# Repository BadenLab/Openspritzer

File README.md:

<p align="right">
<h1 align="center">Openspritzer</h1></p>
<h3 align="center">An open hardware pressure ejection system for reliably delivering picolitre volumes.</h3>
<p align="center"><h6 align="right">by C.J. Forman, H. Tomes, B. Mbobo, R.J. Burman, M. Jacobs, T Baden &
J.V. Raimondo</h6></p>
<p align="center"><h6 align="right">adapted by M.J.Y. Zimmermann</h6></p>

</p>

<p align="justify">Designed for ease of use, robustness and low-cost, the “Openspritzer” is an open hardware “Picospritzer” as routinely used
in biological labs around the world. The performance of Openspritzer and commercial alternatives is effectively indistiguishable.

<p align="justify">The system is based on a solenoid valve connected to a pressure gauge. Control can be attained directly via an external TTL pulse
or internally through an Arduino set by a rotary encoder. The basic setup can be put together for 3-400€, or substantially less if you
are prepare to shop around.

<p align="justify">We anticipate that due to its high performance and low cost Openspritzer will be of interest to a broad range of researchers working
in the life and physical sciences.</p>

This project is licensed under the [GNU General Public License v3.0](https://github.com/BadenLab/Openspritzer/blob/master/LICENSE)<br>
The hardware is licensed under the [CERN OHL v1.2](https://github.com/BadenLab/LED-Zappelin/blob/master/PCB/LICENSE)

***

- [Openspritzer, a DIY opensource microinjector.](#openspritzer-a-diy-opensource-microinjector)
- [Openspritzer rivals the performance of commercial systems.](#openspritzer-rivals-the-performance-of-commercial-systems)
- [Openspritzer in neuroscience experiments.](#openspritzer-in-neuroscience-experiments)
  - [Contributors:](#contributors)

***

## Openspritzer, a DIY opensource microinjector.

<p align="justify">Compared to similar commercial systems that can cost up to several thousand pounds, the cost of the fully equiped Openspritzer (~£350) makes it
particularly attractive for those wishing to pursue cutting-edge techniques in low ressource environments.</p>

This repository contains detailed [assembly instructions](https://github.com/BadenLab/Openspritzer/tree/master/Instruction%20Manual) and an operation manual for Openspritzer. The [bill of material](https://github.com/BadenLab/Openspritzer/blob/master/Bill%20of%20Materials/BOM.csv) details all pneumatic, mechanical and electronic components required along with possible supplier URL links.

To simplify the wiring assembly, we have designed a customed [circuit board](https://github.com/BadenLab/Openspritzer/tree/master/PCB). PCB prototype companies will only need the gerber.zip folder to be sent to them for production.

We used [OpenSCAD](http://openscad.org) to design [3D files](https://github.com/BadenLab/Openspritzer/tree/master/3D%20Designs) that could be printed to efficiently hold all openspritzer components.

The device is controled by an arduino nano. The [.ino code](https://github.com/BadenLab/Openspritzer/tree/master/Arduino%20Code) can be modified and uploaded as many times as you like. The way the Openspritzer code has been constructed allows simple modification of key parameters. These are all included at the beginning of the code for ease of reference.

***

## Openspritzer rivals the performance of commercial systems.

Openspritzer control over dose delivery matches that of a leading commercial alternative.

<p align="justify">To directly assess the time precision and reliability of Openspritzer we visualised fluorescent dye puffs from a sharp microelectrode under two-photon microscopy. The images were taken from a puff with a duration of several seconds using a wide area scan (rectangles).

<p align="justify">Fluorescence profiles of different command-duration puffs are shown for Openspritzer (green) and Picospritzer, a popular microinjection system(purple), respectively. The same data is shown again in log-log space to highlight details of shorter pulses. Overall, both devices behave in a very similar way in terms of providing effective and near linear control over the total dosage.</p>

***

## Openspritzer in neuroscience experiments.

Openspritzer controls neural activity by delivering neurotransmitters with millisecond precision.

<p align="justify">To demonstrate the utility of Openspritzer, we use it in a series of standard neurobiological applications:
We delivered precise amounts of glutamate(cyan) and GABA(orange) to hippocampal neurons to elicit time- and dose-precise excitatory and inhibitory responses respectively, while monitoring the voltage response of the recorded neuron in current-clamp mode.

<p align="justify">20 ms doses of glutamate (100 μM) reliably evoked excitatory postsynaptic potentials (EPSPs) and action potentials. Similarly, action potential activity elicited via somatic current injection could be suppressed by 20 ms puffs of GABA (100 μM).

<p align="justify">To assess the accuracy of the drug delivery, we applied 10 sweeps where a 20 ms glutamate puff was applied after 500 ms produced almost identical EPSPs demonstrating the precise timing of Openspritzer and highly conserved puff volumes.

<p align="justify">Then, to test the effect of command duration on effective dose delivey, we next applied puffs of increasing duration from 10 to 100 ms in 10 ms steps. Here, each additional 10 ms increase in duration produced a clear increase in both EPSP duration and amplitude. These results confirm the reliability and precision of Openspritzer for delivering small doses of an agent to a widely used biological sample in a controlled manner.</p>

***

<p align="justify">To demonstrate the utility of Openspritzer we performed multiple example experiments delivering agents ranging in size from single molecules to whole bacteria. Each experiment depended critically on the performance of the device. The spatio-temporal control of reagent delivery affored by Openspritzer is a primary feature of the device.

<p align="justify">Furthermore, with the emergence of a plethora of popular new techniques involving genetic manipulation of tissue and organisms, such as optogenetics and CRISPR, the demand for equipment with the functionality of Openspritzer is likely to increase.

<p align="justify">We anticipate that due to its high performance and low cost Openspritzer will be of interest to a broad range of researchers working in the life and physical sciences.</p>

<p align="center"><h6 align="right">Source: CJ. Forman et al, 2017 --  https://www.nature.com/articles/s41598-017-02301-2   </h6>

***
### Contributors:

This project is under development for a number of years with contributors from different continents! Here is a small overview:

**2017** formal prototype and publication: 
CJ Forman, H Tomes, RJ Burman M Jacobs, T Baden, JV Raimondo

**2018** creation of PCB, editable designs and 3D printed casing
M Zimmermann, AM Chagas

**2022** Screen add on for pulse duration feedback
J Frie, J Khokhar

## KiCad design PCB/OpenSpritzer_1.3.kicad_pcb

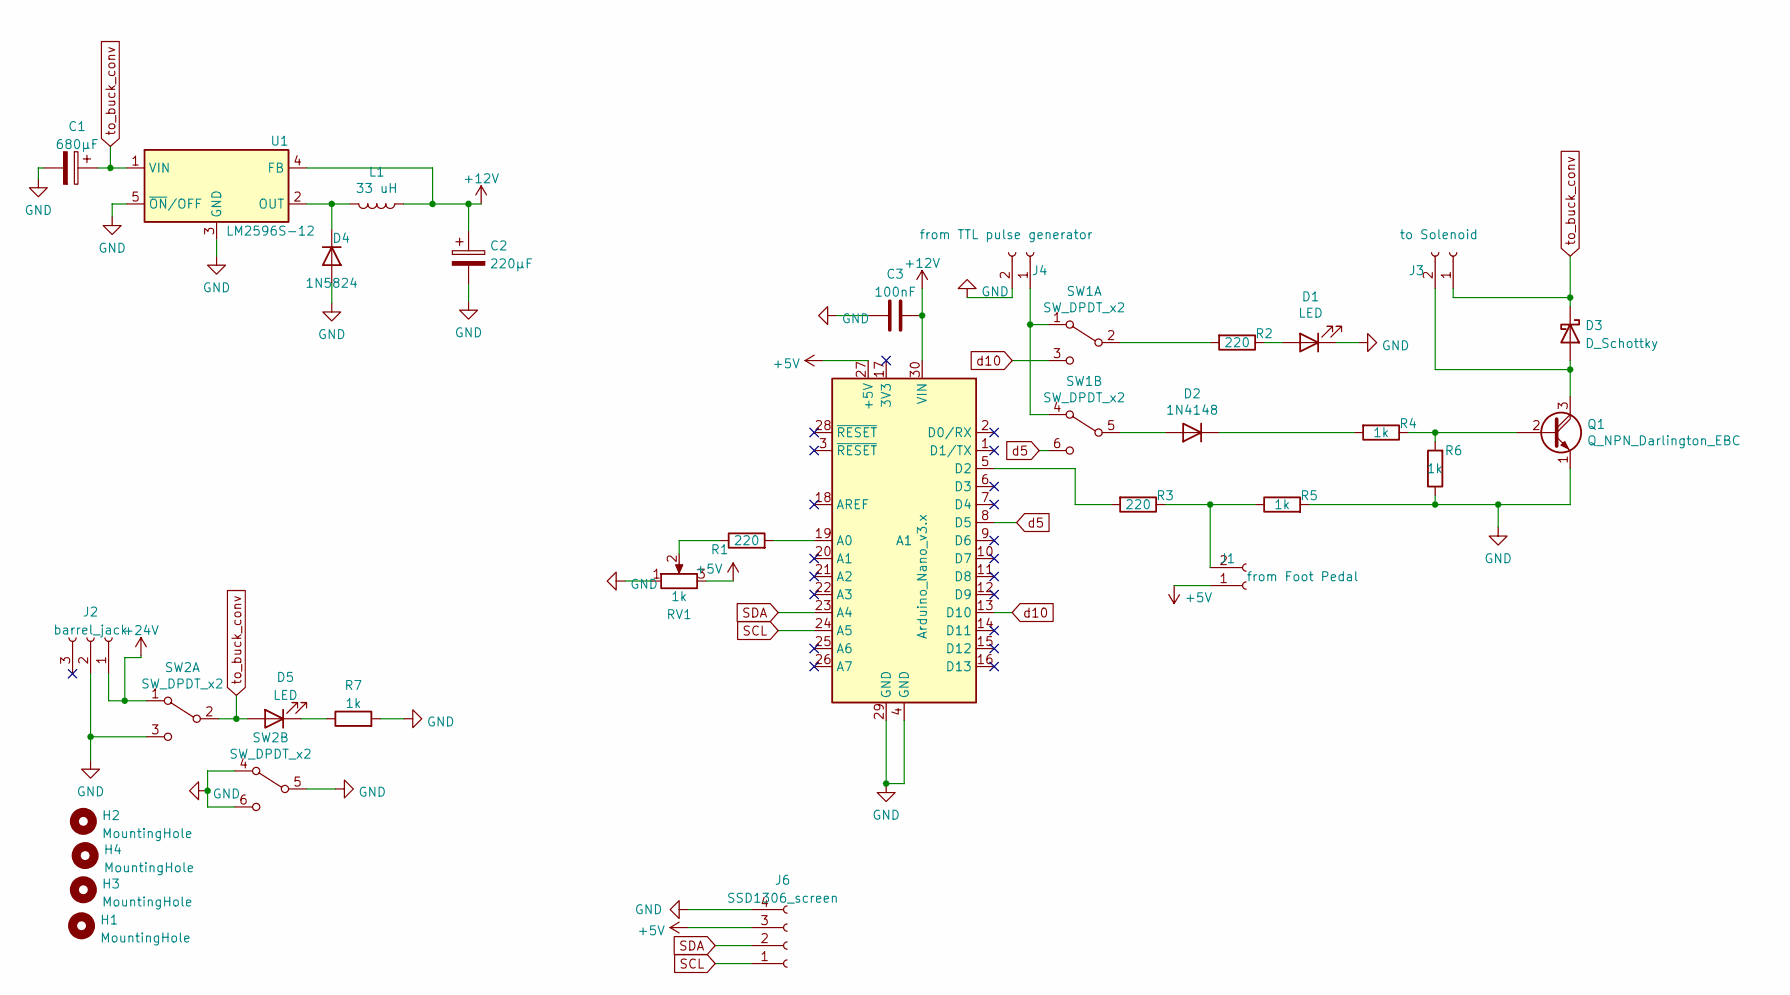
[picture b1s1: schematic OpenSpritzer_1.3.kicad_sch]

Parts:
A1: Arduino_Nano_v3.x; Arduino_Nano
C1: 680µF; CP_Radial_D8.0mm_P3.50mm
C2: 220µF; CP_Radial_D6.3mm_P2.50mm
C3: 100nF; C_Disc_D7.5mm_W4.4mm_P5.00mm
D1, D5: LED; LED_D5.0mm_Horizontal_O1.27mm_Z15.0mm
D2: 1N4148; D_DO-35_SOD27_P7.62mm_Horizontal
D3: D_Schottky; D_DO-27_P15.24mm_Horizontal
D4: 1N5824; D_DO-201AD_P15.24mm_Horizontal
H1, H2, H3, H4: MountingHole; MountingHole_3.2mm_M3_DIN965
J1: from Foot Pedal; BNC_Amphenol_B6252HB-NPP3G-50_Horizontal
J2: barrel_jack; BarrelJack_GCT_DCJ200-10-A_Horizontal
J3: to Solenoid; JST_XH_B2B-XH-A_1x02_P2.50mm_Vertical
J4: from TTL pulse generator; BNC_Amphenol_B6252HB-NPP3G-50_Horizontal
J6: SSD1306_screen; JST_XH_B4B-XH-A_1x04_P2.50mm_Vertical
L1: 33 uH; L_Radial_D6.0mm_P4.00mm
Q1: Q_NPN_Darlington_EBC; TO-92L_Wide
R1, R2, R3: 220; R_Axial_DIN0414_L11.9mm_D4.5mm_P15.24mm_Horizontal
R4, R5, R6, R7: 1k; R_Axial_DIN0414_L11.9mm_D4.5mm_P15.24mm_Horizontal
RV1: 1k; JST_XH_B3B-XH-A_1x03_P2.50mm_Vertical
SW1, SW2: SW_DPDT_x2; SW_Push_2P2T_Vertical_E-Switch_800UDP8P1A1M6
U1: LM2596S-12; TO-220-5_P3.4x3.7mm_StaggerOdd_Lead3.8mm_Vertical

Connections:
+5V: A1.27 (+5V), J1.1, J6.3, RV1.3
+12V: A1.30 (VIN), C2.1, C3.2, L1.1, U1.4 (FB)
+24V: J2.1, SW2.1 (A)
GND: A1.4 (GND), A1.29 (GND), C1.2, C2.2, C3.1, D1.1 (K), D4.2 (A), J2.2, J4.2, J6.4, Q1.1 (E), R5.2, R6.1, R7.2, RV1.1, SW2.3 (C), SW2.4 (A), SW2.5 (B), SW2.6 (C), U1.3 (GND), U1.5 (~ON/OFF)
unnamed: A1.5 (D2), R3.2
unnamed: A1.19 (A0), R1.2
unnamed: D1.2 (A), R2.1
unnamed: D2.1 (K), R4.2
unnamed: D2.2 (A), SW1.5 (B)
unnamed: D3.2 (A), J3.2, Q1.3 (C)
unnamed: D5.1 (K), R7.1
unnamed: J1.2, R3.1, R5.1
unnamed: J4.1, SW1.1 (A), SW1.4 (A)
unnamed: Q1.2 (B), R4.1, R6.2
unnamed: R1.1, RV1.2
unnamed: R2.2, SW1.2 (B)
unnamed: D4.1 (K), L1.2, U1.2 (OUT)
SCL: A1.24 (A5), J6.1
SDA: A1.23 (A4), J6.2
d5: A1.8 (D5), SW1.6 (C)
d10: A1.13 (D10), SW1.3 (C)
to_buck_conv: C1.1, D3.1 (K), D5.2 (A), J3.1, SW2.2 (B), U1.1 (VIN)

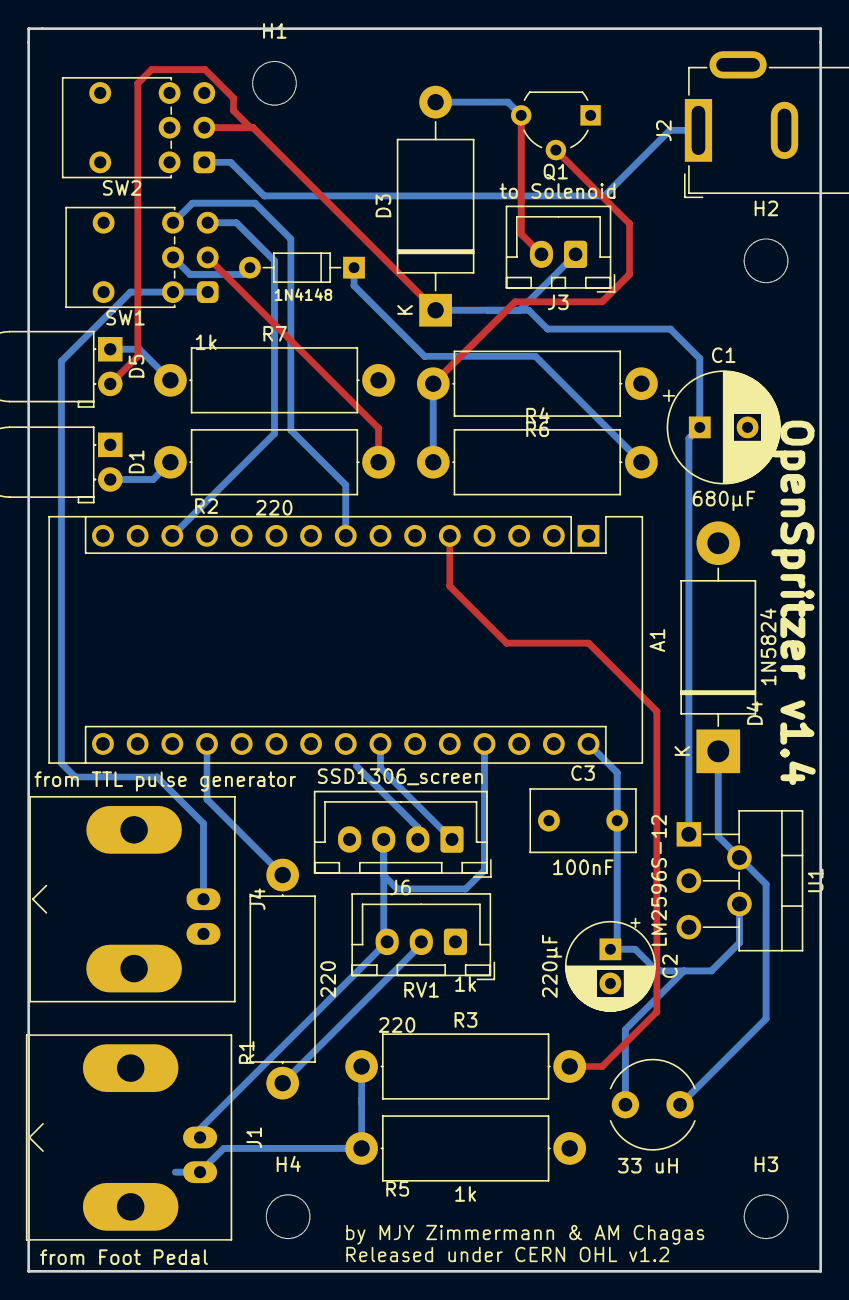
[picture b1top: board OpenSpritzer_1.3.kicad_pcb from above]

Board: 2 copper layers, 58.0 x 91.0 mm, 31 parts (0 on the bottom side), 22 nets.

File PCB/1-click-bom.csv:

References,Qty,Description,Manufacturer,MPN,Manufacturer,MPN,Manufacturer,MPN,Manufacturer,MPN,Digikey,Mouser,RS,Newark,Farnell,LCSC,JLC Assembly
A1,2,2.54 mm header 15 pin 1 row,Samtec inc,SSA-115-S-T,Samtec,SSW-115-01-T-S,Samtec,SSA-115-S-T,,SSW-115-01-T-S,SAM1213-15-ND,200SSW11501TS,1981501,,2779587,,
C1,1,680 uf electrolict cap,Rubycon,35ZLH680MEFC10X23,,,,,,,1189-1749-ND,23235ZLH680MEFC10X2,7037560,,8126771,,
C2,1,220 uf electrolitic cap,Panasonic,EEUFC1V221,Panasonic,EEU-FC1V221,,,,,P10297-ND,667EEUFC1V221,3150726,,9692282,,
"D1,D5",1,Red LED 5mm,kingbright,L-53HD,Kingbright,L-53HD,Vishay,VLCS5830,,,754-2157-ND,78VLCS5830,2285988,,2889660,,
D2,1,1N4148,On Semiconductor,1N4148TR,Vishay,1N4148TR,ON Semiconductor,1N4148TR,,,1N4148FSCT-ND,5121N4148TR,6715477,,9843680,,
"D3,D4",1,"40V 3A, Schottky Diode",STM,1N5822RL,STMicroelectronics,1N5822RL,,,,,497-14742-1-ND,5111N5822TR,7146819,,3214544,,
"J1,J4",2,"Right Angle 50Ω PCB Mount Bulkhead Fitting BNC Connector,",TE connectivity,1-1337542-0,TE Connectivity,,Amphenol,B6252HB-NPP3G-50,,,A97552-ND,571113375420,5121203,,1020954,,
J2,1,Barrel jack,Cliff,FC68148 DC10A,,,,,,,,,,,,,
J3,2,JST Header 2 pin B2B XH series,JST,B2B-XH-A(LF)(SN),,,,,,,455-2247-ND,,8201554,,1516276,,
L1,1,33 μH ±10% Ferrite Radial Inductor,Bourns,RLB0914-330KL,,,,,,,RLB0914-330KL-ND,652RLB0914330KL,8118853,,2309242,,
Q1,1,NPN darlington,Fairchild,KSP 13BU,ON Semiconductor,KSP13BU,,,,,KSP13BU-ND,512KSP13BU,7390344,,2825113,,
"R1, R2, R3",2,220 resistor 250mW,Stackpole electronics,CF14JT220R,Stackpole Electronics,CF14JT220R,,,,,CF14JT220RCT-ND,,,,,,
"R4, R5, R6, R7",3,1k resistor 250mW,Yageo,SQP500JB-1K,TE Connectivity,CFR16J1K0,,,,,1.0KW-5-ND,603SQP500JB1K,1251150,,2329486,,
RV1,1,1k 1W 10% potentiometer,Vishay,249FGJS0XB25102KA,Bourns,51CAD-E28-A10L,,,,,51CAD-E28-A10L-ND,65251CADE28A10L,410176,,1107271,,
"SW1, SW2",2,DPDT,Multicomp,2MD3T2B2M6RE,,,,,,,,,7347205,,1550091,,
U1,1,step down voltage regulator,Texas instruments,LM2596T-12/NOPB,Texas Instruments,LM2596T-12/NOPB,,,,,LM2596T-12/NOPB-ND,926LM2596T12/NOPB,5333721,,1693993,,
A1,1,Arduino Nano,,,,,,,,,,,,,,,
C3,1,100nf ceramic capacitor,,,,,,,,,478-5117-ND,581AR215C104K4R,6994891,,,,
J6,1,connector for screen,JST,B4B-XH-A,JST,B4B-XH-A(LF)(SN),,,,,,,8201551,,,,

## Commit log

2018-07-26 created PCB, missing outline and screw pads
2018-07-27 update board. Main is done
2018-07-27 board with hardware licence and links
2018-07-27 final_version0.1
2018-08-07 pcb addon
2018-08-07 PCB Board
2018-08-07 README update
2018-08-07 2018.08.07
2018-08-07 2018.08.7
2018-08-08 2018.08.08
2018-08-09 https://www.nature.com/articles/s41598-017-02301-2
2018-09-07 Version 1.01
2018-09-09 version 1.02
2018-10-02 v1.02
2018-10-02 V 1.02
2018-10-08 v 1.2
2018-10-11 README.md
2018-10-11 Pneumatic Data Sheets
2018-10-11 V1.2
2018-10-11 Bill of Materials
2018-10-11 v0.1
2018-10-11 Arduino Code
2018-10-11 Images
2018-10-11 Supplementary Instructions
2018-12-07 v1.3
2018-12-12 v 1.3
2019-02-24 Create LICENSE
2019-10-15 create manifest for open spritzer
2020-08-03 rename gerber to gerbers and start working on 1-click-bom.tsv
2020-08-06 update boms
2020-08-08 update 1-click-bom
2022-04-06 update PCB and port it to KiCAD 6
2022-04-10 add information about contributors and J Frie screen add on
2022-04-10 add i2c pin layout
2022-08-02 update PCB
2022-09-09 update footprints
2022-10-12 update new board
2022-10-13 bump pcb version number and prepare for kitspace

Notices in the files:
PCB/OpenSpritzer_1.3.kicad_pcb:
Released under CERN OHL v1.2
